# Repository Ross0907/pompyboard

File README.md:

# Wonkle

Wonkle builds gaming hardware such as tablets and keypads for gamers.
Source code, 3D models, schematics, etc. are available under
[OSI-Approved Software and Hardware Licenses](https://opensource.org/licenses). We welcome everyone
to contribute and join us in our quest to make the best hardware for our fellow gamers.

## [Frequently Asked Questions](https://docs.wonkle.io/faq.html)

## Star History

## Contributors

Wonkle is built by people like you.

## License

Different parts of the project are available under different licenses.

All image, audio, and other resources are, unless otherwise specified, available under
[`CC-BY-4.0`](https://spdx.org/licenses/CC-BY-4.0.html).

The hardware designs are, unless otherwise specified, available under
[`CERN-OHL-S-2.0`](https://spdx.org/licenses/CERN-OHL-S-2.0.html).

All other code are, unless otherwise specified, available under
[`MIT`](https://spdx.org/licenses/MIT.html).

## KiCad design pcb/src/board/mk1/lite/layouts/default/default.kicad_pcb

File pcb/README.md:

# PCB

Designed with [KiCad][kicad].

## Designing

- Every PCB is designed with KiCad `v10.0.3`.
- you can learn more about each of the components and read their documentations at
  [`docs/components`](./docs/components/README.md).
  Running `bun run gen-docs` will download PDF documentations.

## Manufacturing

Both prototype and production PCB is manufactured by [JLCPCB][jlcpcb].

### Steps

1. Install [KiCad][kicad].
2. Install the [Fabrication Toolkit][fab-toolkit] plugin.
3. "Generate" production files using the plugin with default settings.
4. Go to [jlcpcb.com][jlcpcb] and click "Add gerber file"
5. Select `pcb/production/wonkle.zip`
6. Configure PCB (you will get 5 pcb of which 2 have components soldered)
   - PCB Specifications
     - PCB Thickness - 1.0mm
     - Surface Finish - LeadFree HASL (health is important boiz)
   - High-spec Options
     - Confirm Production file - Yes
     - Mark on PCB - Order Number(Specify Position)
   - PCB Assembly
     - PCBA Qty - minimum is 2
     - Confirm Parts Placement - Yes
     - Advanced
       - Board Cleaning - Yes
7. Press "NEXT"
8. Inspect PCB and press "NEXT" again
9. Upload and process `pcb/production/bom.csv` and `pcb/production/positions.csv`
10. Review the parts and press "NEXT"
11. Fix component placement
    - only J2 (1x4 pin) needs manual edit
12. Select `Research\Education\DIY\Entertainment > DIY Hobby Circuit Board - HS Code 902300` in Quote & Order section. The total price is 137.13 USD as of writing.
13. Press "SAVE TO CART"
14. Select both PCB and PCBA then click "Secure Checkout"
15. Enter shipping info and follow JLCPCB's instruction (e.g. production file confirmation)
16. Wait for a week and you'll receive your very own board!

[kicad]: https://www.kicad.org/
[jlcpcb]: https://jlcpcb.com/
[fab-toolkit]: https://github.com/bennymeg/Fabrication-Toolkit

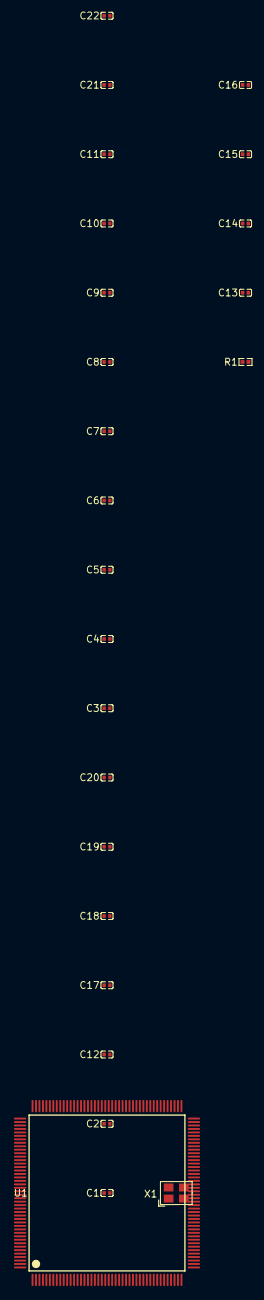
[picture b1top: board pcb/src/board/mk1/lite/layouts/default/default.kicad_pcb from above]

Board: 2 copper layers, 25 parts (0 on the bottom side), 7 nets, no tracks yet.

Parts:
C1: 4.7µF ±20%; C0402
C2, C3, C4, C5, C6, C7, C8, C9, C10, C11, C12, C17, C18, C19, C20: 100nF ±10%; C0402
C13, C14: 20pF ±5%; C0402
C15, C16: 2.2µF ±20%; C0402
C21: 1µF ±10%; C0402
C22: 10nF ±10%; C0402
R1: 1kΩ ±1%; R0402
U1: LQFP-176_L24.0-W24.0-P0.50-LS26.0-BL
X1: CRYSTAL-SMD_4P-L3.2-W2.5-BL-2

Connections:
XIN: C13.1, U1.29, X1.1
XOUT: R1.2, U1.30
hse_load_caps[1]-power-hv: C14.1, R1.1, X1.3
hv: C1.1, C2.1, C3.1, C4.1, C5.1, C6.1, C7.1, C8.1, C9.1, C10.1, C11.1, C12.1, C17.1, C18.1, C19.1, C20.1, C21.1, C22.1, U1.6, U1.15, U1.23, U1.36, U1.38, U1.39, U1.49, U1.62, U1.72, U1.82, U1.91, U1.103, U1.114, U1.127, U1.136, U1.149, U1.159, U1.172
lv: C1.2, C2.2, C3.2, C4.2, C5.2, C6.2, C7.2, C8.2, C9.2, C10.2, C11.2, C12.2, C13.2, C14.2, C15.2, C16.2, C17.2, C18.2, C19.2, C20.2, C21.2, C22.2, U1.14, U1.22, U1.37, U1.61, U1.71, U1.90, U1.102, U1.113, U1.126, U1.135, U1.148, U1.158, X1.2, X1.4
vcap_caps[0]-power-hv: C15.1, U1.81
vcap_caps[1]-power-hv: C16.1, U1.125

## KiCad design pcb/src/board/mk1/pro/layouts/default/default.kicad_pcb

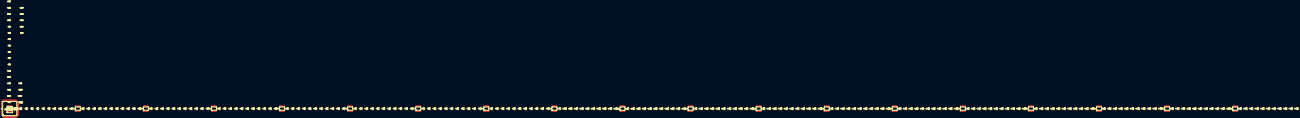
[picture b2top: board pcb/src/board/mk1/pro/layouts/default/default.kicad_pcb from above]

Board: 2 copper layers, 260 parts (0 on the bottom side), 243 nets, no tracks yet.

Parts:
C1: 4.7µF ±20%; C0402
C2, C3, C4, C5, C6, C7, C8, C9, C10, C11, C12, C17, C18, C22, C23: 100nF ±10%; C0402
C13, C14: 20pF ±5%; C0402
C15, C16: 2.2µF ±20%; C0402
C19: 10µF ±20%; C0402
C20: 22µF ±20%; C0402
C21: 3.3nF ±10%; C0402
C24: 1µF ±10%; C0402
C25: 10nF ±10%; C0402
L1: L 2.2µH ±10%; L0805
R1: 1kΩ ±1%; R0402
R2: 100kΩ ±1%; R0603
U1: LQFP-176_L24.0-W24.0-P0.50-LS26.0-BL
U2, U14, U26, U38, U50, U62, U74, U86, U98, U110, U122, U134, U146, U158, U170, U182, U194, U206, U218: SSOP-24_L8.1-W5.3-P0.65-LS7.8-BL
U3, U4, U5, U6, U7, U8, U9, U10, U11, U12, U13, U15, U16, U17, U18, U19, U20, U21, U22, U23, U24, U25, U27, U28, U29, U30, U31, U32, U33, U34, U35, U36, U37, U39, U40, U41, U42, U43, U44, U45, U46, U47, U48, U49, U51, U52, U53, U54, U55, U56, U57, U58, U59, U60, U61, U63, U64, U65, U66, U67, U68, U69, U70, U71, U72, U73, U75, U76, U77, U78, U79, U80, U81, U82, U83, U84, U85, U87, U88, U89, U90, U91, U92, U93, U94, U95, U96, U97, U99, U100, U101, U102, U103, U104, U105, U106, U107, U108, U109, U111, U112, U113, U114, U115, U116, U117, U118, U119, U120, U121, U123, U124, U125, U126, U127, U128, U129, U130, U131, U132, U133, U135, U136, U137, U138, U139, U140, U141, U142, U143, U144, U145, U147, U148, U149, U150, U151, U152, U153, U154, U155, U156, U157, U159, U160, U161, U162, U163, U164, U165, U166, U167, U168, U169, U171, U172, U173, U174, U175, U176, U177, U178, U179, U180, U181, U183, U184, U185, U186, U187, U188, U189, U190, U191, U192, U193, U195, U196, U197, U198, U199, U200, U201, U202, U203, U204, U205, U207, U208, U209, U210, U211, U212, U213, U214, U215, U216, U217, U219, U220, U221, U222, U223, U224, U225, U226, U227, U228, U229: SOT-23-3_L2.9-W1.6-P1.90-LS2.8-BR
U230: TQFN-16_L3.0-W3.0-P0.50-TL-EP1.7
USB1: USC-C-SMD_USB4085-GF-A
X1: CRYSTAL-SMD_4P-L3.2-W2.5-BL-2

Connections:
2: U2.2, U13.2
OUT: U1.41, U134.1
PG: R2.2, U230.4
S0: U1.5, U2.10, U14.10, U26.10, U38.10, U50.10, U62.10, U74.10, U86.10, U98.10, U110.10, U122.10, U134.10, U146.10, U158.10, U170.10, U182.10, U194.10, U206.10, U218.10
S1: U1.4, U2.11, U14.11, U26.11, U38.11, U50.11, U62.11, U74.11, U86.11, U98.11, U110.11, U122.11, U134.11, U146.11, U158.11, U170.11, U182.11, U194.11, U206.11, U218.11
S2: U1.3, U2.14, U14.14, U26.14, U38.14, U50.14, U62.14, U74.14, U86.14, U98.14, U110.14, U122.14, U134.14, U146.14, U158.14, U170.14, U182.14, U194.14, U206.14, U218.14
S3: U1.2, U2.13, U14.13, U26.13, U38.13, U50.13, U62.13, U74.13, U86.13, U98.13, U110.13, U122.13, U134.13, U146.13, U158.13, U170.13, U182.13, U194.13, U206.13, U218.13
SW: L1.1, U230.1, U230.2, U230.3
XIN: C13.1, U1.29, X1.1
XOUT: R1.2, U1.30
gpio_a[2]-OUT: U1.42, U146.1
gpio_a[3]-OUT: U1.47, U158.1
gpio_a[4]-OUT: U1.50, U170.1
gpio_a[6]-OUT: U1.52, U182.1
gpio_a[7]-OUT: U1.53, U194.1
gpio_c[2]-OUT: U1.34, U110.1
gpio_c[3]-OUT: U1.35, U122.1
gpio_c[4]-OUT: U1.54, U206.1
gpio_c[5]-OUT: U1.55, U218.1
gpio_f[3]-OUT: U1.19, U2.1
gpio_f[4]-OUT: U1.20, U14.1
gpio_f[5]-OUT: U1.21, U26.1
gpio_f[6]-OUT: U1.24, U38.1
gpio_f[7]-OUT: U1.25, U50.1
gpio_f[8]-OUT: U1.26, U62.1
gpio_f[9]-OUT: U1.27, U74.1
gpio_f[10]-OUT: U1.28, U86.1
hse_load_caps[1]-power-hv: C14.1, R1.1, X1.3
hv: C19.1, U230.10, U230.11, U230.12, U230.13, USB1.A4, USB1.A9, USB1.B4, USB1.B9
i2c[1]-SDA: U1.33, U98.1
lv: C1.2, C2.2, C3.2, C4.2, C5.2, C6.2, C7.2, C8.2, C9.2, C10.2, C11.2, C12.2, C13.2, C14.2, C15.2, C16.2, C17.2, C18.2, C19.2, C20.2, C21.2, C22.2, C23.2, C24.2, C25.2, U1.14, U1.22, U1.37, U1.61, U1.71, U1.90, U1.102, U1.113, U1.126, U1.135, U1.148, U1.158, U2.12, U2.15, U2.16, U2.17, U2.18, U2.19, U2.20, U3.3, U4.3, U5.3, U6.3, U7.3, U8.3, U9.3, U10.3, U11.3, U12.3, U13.3, U14.12, U14.15, U14.16, U14.17, U14.18, U14.19, U14.20, U15.3, U16.3, U17.3, U18.3, U19.3, U20.3, U21.3, U22.3, U23.3, U24.3, U25.3, U26.12, U26.15, U26.16, U26.17, U26.18, U26.19, U26.20, U27.3, U28.3, U29.3, U30.3, U31.3, U32.3, U33.3, U34.3, U35.3, U36.3, U37.3, U38.12, U38.15, U38.16, U38.17, U38.18, U38.19, U38.20, U39.3, U40.3, U41.3, U42.3, U43.3, U44.3, U45.3, U46.3, U47.3, U48.3, U49.3, U50.12, U50.15, U50.16, U50.17, U50.18, U50.19, U50.20, U51.3, U52.3, U53.3, U54.3, U55.3, U56.3, U57.3, U58.3, U59.3, U60.3, U61.3, U62.12, U62.15, U62.16, U62.17, U62.18, U62.19, U62.20, U63.3, U64.3, U65.3, U66.3, U67.3, U68.3, U69.3, U70.3, U71.3, U72.3, U73.3, U74.12, U74.15, U74.16, U74.17, U74.18, U74.19, U74.20, U75.3, U76.3, U77.3, U78.3, U79.3, U80.3, U81.3, U82.3, U83.3, U84.3, U85.3, U86.12, U86.15, U86.16, U86.17, U86.18, U86.19, U86.20, U87.3, U88.3, U89.3, U90.3, U91.3, U92.3, U93.3, U94.3, U95.3, U96.3, U97.3, U98.12, U98.15, U98.16, U98.17, U98.18, U98.19, U98.20, U99.3, U100.3, U101.3, U102.3, U103.3, U104.3, U105.3, U106.3, U107.3, U108.3, U109.3, U110.12, U110.15, U110.16, U110.17, U110.18, U110.19, U110.20, U111.3, U112.3, U113.3, U114.3, U115.3, U116.3, U117.3, U118.3, U119.3, U120.3, U121.3, U122.12, U122.15, U122.16, U122.17, U122.18, U122.19, U122.20, U123.3, U124.3, U125.3, U126.3, U127.3, U128.3, U129.3, U130.3, U131.3, U132.3, U133.3, U134.12, U134.15, U134.16, U134.17, U134.18, U134.19, U134.20, U135.3, U136.3, U137.3, U138.3, U139.3, U140.3, U141.3, U142.3, U143.3, U144.3, U145.3, U146.12, U146.15, U146.16, U146.17, U146.18, U146.19, U146.20, U147.3, U148.3, U149.3, U150.3, U151.3, U152.3, U153.3, U154.3, U155.3, U156.3, U157.3, U158.12, U158.15, U158.16, U158.17, U158.18, U158.19, U158.20, U159.3, U160.3, U161.3, U162.3, U163.3, U164.3, U165.3, U166.3, U167.3, U168.3, U169.3, U170.12, U170.15, U170.16, U170.17, U170.18, U170.19, U170.20, U171.3, U172.3, U173.3, U174.3, U175.3, U176.3, U177.3, U178.3, U179.3, U180.3, U181.3, U182.12, U182.15, U182.16, U182.17, U182.18, U182.19, U182.20, U183.3, U184.3, U185.3, U186.3, U187.3, U188.3, U189.3, U190.3, U191.3, U192.3, U193.3, U194.12, U194.15, U194.16, U194.17, U194.18, U194.19, U194.20, U195.3, U196.3, U197.3, U198.3, U199.3, U200.3, U201.3, U202.3, U203.3, U204.3, U205.3, U206.12, U206.15, U206.16, U206.17, U206.18, U206.19, U206.20, U207.3, U208.3, U209.3, U210.3, U211.3, U212.3, U213.3, U214.3, U215.3, U216.3, U217.3, U218.12, U218.15, U218.16, U218.17, U218.18, U218.19, U218.20, U219.3, U220.3, U221.3, U222.3, U223.3, U224.3, U225.3, U226.3, U227.3, U228.3, U229.3, U230.5, U230.6, U230.7, U230.8, U230.15, U230.16, USB1.A1, USB1.A12, USB1.B1, USB1.B12, X1.2, X1.4
mux-OUT: U2.21, U3.2
mux-OUT-1: U2.22, U4.2
mux-OUT-2: U2.23, U5.2
mux-OUT-3: U2.3, U12.2
mux-OUT-4: U2.4, U11.2
mux-OUT-5: U2.5, U10.2
mux-OUT-6: U2.6, U9.2
mux-OUT-7: U2.7, U8.2
mux-OUT-8: U2.8, U7.2
mux-OUT-9: U2.9, U6.2
mux-OUT-10: U122.21, U123.2
mux-OUT-11: U122.22, U124.2
mux-OUT-12: U122.23, U125.2
mux-OUT-13: U122.3, U132.2
mux-OUT-14: U122.4, U131.2
mux-OUT-15: U122.5, U130.2
mux-OUT-16: U122.6, U129.2
mux-OUT-17: U122.7, U128.2
mux-OUT-18: U122.8, U127.2
mux-OUT-19: U122.9, U126.2
mux-OUT-20: U134.21, U135.2
mux-OUT-21: U134.22, U136.2
mux-OUT-22: U134.23, U137.2
mux-OUT-23: U134.3, U144.2
mux-OUT-24: U134.4, U143.2
mux-OUT-25: U134.5, U142.2
mux-OUT-26: U134.6, U141.2
mux-OUT-27: U134.7, U140.2
mux-OUT-28: U134.8, U139.2
mux-OUT-29: U134.9, U138.2
mux-OUT-30: U146.21, U147.2
mux-OUT-31: U146.22, U148.2
mux-OUT-32: U146.23, U149.2
mux-OUT-33: U146.3, U156.2
mux-OUT-34: U146.4, U155.2
mux-OUT-35: U146.5, U154.2
mux-OUT-36: U146.6, U153.2
mux-OUT-37: U146.7, U152.2
mux-OUT-38: U146.8, U151.2
mux-OUT-39: U146.9, U150.2
mux-OUT-40: U158.21, U159.2
mux-OUT-41: U158.22, U160.2
mux-OUT-42: U158.23, U161.2
mux-OUT-43: U158.3, U168.2
mux-OUT-44: U158.4, U167.2
mux-OUT-45: U158.5, U166.2
mux-OUT-46: U158.6, U165.2
mux-OUT-47: U158.7, U164.2
mux-OUT-48: U158.8, U163.2
mux-OUT-49: U158.9, U162.2
mux-OUT-50: U170.21, U171.2
mux-OUT-51: U170.22, U172.2
mux-OUT-52: U170.23, U173.2
mux-OUT-53: U170.3, U180.2
mux-OUT-54: U170.4, U179.2
mux-OUT-55: U170.5, U178.2
mux-OUT-56: U170.6, U177.2
mux-OUT-57: U170.7, U176.2
mux-OUT-58: U170.8, U175.2
mux-OUT-59: U170.9, U174.2
mux-OUT-60: U182.21, U183.2
mux-OUT-61: U182.22, U184.2
mux-OUT-62: U182.23, U185.2
mux-OUT-63: U182.3, U192.2
mux-OUT-64: U182.4, U191.2
mux-OUT-65: U182.5, U190.2
mux-OUT-66: U182.6, U189.2
mux-OUT-67: U182.7, U188.2
mux-OUT-68: U182.8, U187.2
mux-OUT-69: U182.9, U186.2
mux-OUT-70: U194.21, U195.2
mux-OUT-71: U194.22, U196.2
mux-OUT-72: U194.23, U197.2
mux-OUT-73: U194.3, U204.2
mux-OUT-74: U194.4, U203.2
mux-OUT-75: U194.5, U202.2
mux-OUT-76: U194.6, U201.2
mux-OUT-77: U194.7, U200.2
mux-OUT-78: U194.8, U199.2
mux-OUT-79: U194.9, U198.2
mux-OUT-80: U206.21, U207.2
mux-OUT-81: U206.22, U208.2
mux-OUT-82: U206.23, U209.2
mux-OUT-83: U206.3, U216.2
mux-OUT-84: U206.4, U215.2
mux-OUT-85: U206.5, U214.2
mux-OUT-86: U206.6, U213.2
mux-OUT-87: U206.7, U212.2
mux-OUT-88: U206.8, U211.2
mux-OUT-89: U206.9, U210.2
mux-OUT-90: U218.21, U219.2
mux-OUT-91: U218.22, U220.2
mux-OUT-92: U218.23, U221.2
mux-OUT-93: U218.3, U228.2
mux-OUT-94: U218.4, U227.2
mux-OUT-95: U218.5, U226.2
mux-OUT-96: U218.6, U225.2
mux-OUT-97: U218.7, U224.2
mux-OUT-98: U218.8, U223.2
mux-OUT-99: U218.9, U222.2
mux-OUT-100: U14.21, U15.2
mux-OUT-101: U14.22, U16.2
mux-OUT-102: U14.23, U17.2
mux-OUT-103: U14.3, U24.2
mux-OUT-104: U14.4, U23.2
mux-OUT-105: U14.5, U22.2
mux-OUT-106: U14.6, U21.2
mux-OUT-107: U14.7, U20.2
mux-OUT-108: U14.8, U19.2
mux-OUT-109: U14.9, U18.2
mux-OUT-110: U26.21, U27.2
mux-OUT-111: U26.22, U28.2
mux-OUT-112: U26.23, U29.2
mux-OUT-113: U26.3, U36.2
mux-OUT-114: U26.4, U35.2
mux-OUT-115: U26.5, U34.2
mux-OUT-116: U26.6, U33.2
mux-OUT-117: U26.7, U32.2
mux-OUT-118: U26.8, U31.2
mux-OUT-119: U26.9, U30.2
mux-OUT-120: U38.21, U39.2
mux-OUT-121: U38.22, U40.2
mux-OUT-122: U38.23, U41.2
mux-OUT-123: U38.3, U48.2
mux-OUT-124: U38.4, U47.2
mux-OUT-125: U38.5, U46.2
mux-OUT-126: U38.6, U45.2
mux-OUT-127: U38.7, U44.2
mux-OUT-128: U38.8, U43.2
mux-OUT-129: U38.9, U42.2
mux-OUT-130: U50.21, U51.2
mux-OUT-131: U50.22, U52.2
mux-OUT-132: U50.23, U53.2
mux-OUT-133: U50.3, U60.2
mux-OUT-134: U50.4, U59.2
mux-OUT-135: U50.5, U58.2
mux-OUT-136: U50.6, U57.2
mux-OUT-137: U50.7, U56.2
mux-OUT-138: U50.8, U55.2
mux-OUT-139: U50.9, U54.2
mux-OUT-140: U62.21, U63.2
mux-OUT-141: U62.22, U64.2
mux-OUT-142: U62.23, U65.2
mux-OUT-143: U62.3, U72.2
mux-OUT-144: U62.4, U71.2
mux-OUT-145: U62.5, U70.2
mux-OUT-146: U62.6, U69.2
mux-OUT-147: U62.7, U68.2
mux-OUT-148: U62.8, U67.2
mux-OUT-149: U62.9, U66.2
mux-OUT-150: U74.21, U75.2
mux-OUT-151: U74.22, U76.2
mux-OUT-152: U74.23, U77.2
mux-OUT-153: U74.3, U84.2
mux-OUT-154: U74.4, U83.2
mux-OUT-155: U74.5, U82.2
mux-OUT-156: U74.6, U81.2
mux-OUT-157: U74.7, U80.2
mux-OUT-158: U74.8, U79.2
mux-OUT-159: U74.9, U78.2
mux-OUT-160: U86.21, U87.2
mux-OUT-161: U86.22, U88.2
mux-OUT-162: U86.23, U89.2
mux-OUT-163: U86.3, U96.2
mux-OUT-164: U86.4, U95.2
mux-OUT-165: U86.5, U94.2
mux-OUT-166: U86.6, U93.2
mux-OUT-167: U86.7, U92.2
mux-OUT-168: U86.8, U91.2
mux-OUT-169: U86.9, U90.2
mux-OUT-170: U98.21, U99.2
mux-OUT-171: U98.22, U100.2
mux-OUT-172: U98.23, U101.2
mux-OUT-173: U98.3, U108.2
mux-OUT-174: U98.4, U107.2
mux-OUT-175: U98.5, U106.2
mux-OUT-176: U98.6, U105.2
mux-OUT-177: U98.7, U104.2
mux-OUT-178: U98.8, U103.2
mux-OUT-179: U98.9, U102.2
mux-OUT-180: U110.21, U111.2
mux-OUT-181: U110.22, U112.2
mux-OUT-182: U110.23, U113.2
mux-OUT-183: U110.3, U120.2
mux-OUT-184: U110.4, U119.2
mux-OUT-185: U110.5, U118.2
mux-OUT-186: U110.6, U117.2
mux-OUT-187: U110.7, U116.2
mux-OUT-188: U110.8, U115.2
mux-OUT-189: U110.9, U114.2
mux_columns[1]-2: U14.2, U25.2
mux_columns[2]-2: U26.2, U37.2
mux_columns[3]-2: U38.2, U49.2
mux_columns[4]-2: U50.2, U61.2
mux_columns[5]-2: U62.2, U73.2
mux_columns[6]-2: U74.2, U85.2
mux_columns[7]-2: U86.2, U97.2
mux_columns[8]-2: U98.2, U109.2
mux_columns[9]-2: U110.2, U121.2
mux_columns[10]-2: U122.2, U133.2
mux_columns[11]-2: U134.2, U145.2
mux_columns[12]-2: U146.2, U157.2
mux_columns[13]-2: U158.2, U169.2
mux_columns[14]-2: U170.2, U181.2
mux_columns[15]-2: U182.2, U193.2
mux_columns[16]-2: U194.2, U205.2
mux_columns[17]-2: U206.2, U217.2
mux_columns[18]-2: U218.2, U229.2
out_cap-power-hv: C1.1, C2.1, C3.1, C4.1, C5.1, C6.1, C7.1, C8.1, C9.1, C10.1, C11.1, C12.1, C17.1, C18.1, C20.1, C22.1, C23.1, C24.1, C25.1, L1.2, R2.1, U1.6, U1.15, U1.23, U1.36, U1.38, U1.39, U1.49, U1.62, U1.72, U1.82, U1.91, U1.103, U1.114, U1.127, U1.136, U1.149, U1.159, U1.172, U2.24, U3.1, U4.1, U5.1, U6.1, U7.1, U8.1, U9.1, U10.1, U11.1, U12.1, U13.1, U14.24, U15.1, U16.1, U17.1, U18.1, U19.1, U20.1, U21.1, U22.1, U23.1, U24.1, U25.1, U26.24, U27.1, U28.1, U29.1, U30.1, U31.1, U32.1, U33.1, U34.1, U35.1, U36.1, U37.1, U38.24, U39.1, U40.1, U41.1, U42.1, U43.1, U44.1, U45.1, U46.1, U47.1, U48.1, U49.1, U50.24, U51.1, U52.1, U53.1, U54.1, U55.1, U56.1, U57.1, U58.1, U59.1, U60.1, U61.1, U62.24, U63.1, U64.1, U65.1, U66.1, U67.1, U68.1, U69.1, U70.1, U71.1, U72.1, U73.1, U74.24, U75.1, U76.1, U77.1, U78.1, U79.1, U80.1, U81.1, U82.1, U83.1, U84.1, U85.1, U86.24, U87.1, U88.1, U89.1, U90.1, U91.1, U92.1, U93.1, U94.1, U95.1, U96.1, U97.1, U98.24, U99.1, U100.1, U101.1, U102.1, U103.1, U104.1, U105.1, U106.1, U107.1, U108.1, U109.1, U110.24, U111.1, U112.1, U113.1, U114.1, U115.1, U116.1, U117.1, U118.1, U119.1, U120.1, U121.1, U122.24, U123.1, U124.1, U125.1, U126.1, U127.1, U128.1, U129.1, U130.1, U131.1, U132.1, U133.1, U134.24, U135.1, U136.1, U137.1, U138.1, U139.1, U140.1, U141.1, U142.1, U143.1, U144.1, U145.1, U146.24, U147.1, U148.1, U149.1, U150.1, U151.1, U152.1, U153.1, U154.1, U155.1, U156.1, U157.1, U158.24, U159.1, U160.1, U161.1, U162.1, U163.1, U164.1, U165.1, U166.1, U167.1, U168.1, U169.1, U170.24, U171.1, U172.1, U173.1, U174.1, U175.1, U176.1, U177.1, U178.1, U179.1, U180.1, U181.1, U182.24, U183.1, U184.1, U185.1, U186.1, U187.1, U188.1, U189.1, U190.1, U191.1, U192.1, U193.1, U194.24, U195.1, U196.1, U197.1, U198.1, U199.1, U200.1, U201.1, U202.1, U203.1, U204.1, U205.1, U206.24, U207.1, U208.1, U209.1, U210.1, U211.1, U212.1, U213.1, U214.1, U215.1, U216.1, U217.1, U218.24, U219.1, U220.1, U221.1, U222.1, U223.1, U224.1, U225.1, U226.1, U227.1, U228.1, U229.1, U230.14
ss_tr_cap-power-hv: C21.1, U230.9
vcap_caps[0]-power-hv: C15.1, U1.81
vcap_caps[1]-power-hv: C16.1, U1.125

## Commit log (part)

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2026-05-06 web: update react (security patch)
2026-05-06 update mise lockfile
2026-05-29 Update PCB with HSE oscillator, Footprint Mismatch fix and Rename project files to Wonkle (#36)
2026-05-29 update license
2026-05-29 put mk1 hardware design under its own subdirectory
2026-05-29 init wonkleboard mk.1 lite as empty atopile project
2026-05-29 automate spelling checks
2026-06-01 pcb: add basic STM32F429 MCU module
2026-06-01 ignore spelling of non-handwritten files
2026-06-02 define and apply github labels
2026-06-02 make github action happy
2026-06-02 rename `type:suggestion` label to `type:proposition`
2026-06-02 rename workflow job to be more appropriate
2026-06-02 order labels alphabetically
2026-06-02 docs: improve clarity in language
2026-06-02 simplify vscode config
2026-06-02 remove unnecessary words from cspell.yaml
2026-06-04 create space to redesign wonkleboard mk.1 pro with atopile
2026-06-04 pcb: initialize Wonkleboard mk.1 Pro atopile project
2026-06-04 pcb: make atopile source code consistent
2026-06-04 pcb: make CI build more robust
2026-06-05 pcb: remove unnecessary pragma directives
2026-06-05 pcb: add MCU to Wonkleboard mk.1 Pro
2026-06-09 make ./scripts intellisense work in vscode
2026-06-09 spell check dot directories
2026-06-13 firmware: run cargo audit in CI
2026-06-13 firmware: disable cargo audit for now
2026-06-16 make firmware work somewhat
2026-06-16 remove unnecessary svd file
2026-06-16 firmware: update stm32f4xx-hal
2026-06-22 pcb: add MUX and sensors to Wonkleboard mk.1 Pro
2026-06-22 pcb: oops forgot to commit this
2026-06-23 pcb: add buck converter
2026-06-23 pcb: add STM32 ADC application note
2026-06-24 pcb: document ADC-capable pins
2026-06-24 pcb: add more bookmarks for STM32F429 datasheet and reference manual
2026-06-24 firmware: add link to HAL source code
2026-06-24 firmware: mention microprocessor docs in README
2026-06-25 pcb: add more references to documentation
2026-06-25 pcb: add decoupling capacitors to STM32F429
2026-06-25 add AGENTS.md
2026-06-27 firmware: v0.1 baseline (#61)
2026-06-27 fix cspell prune script
2026-06-27 pcb: migrate from atopile to tscircuit (tsci init)
2026-06-27 pcb: add PDF files to gitignore
2026-06-27 pcb: add STM32F429IGT6
2026-06-27 pcb: add KiCad files to gitignore
2026-06-27 pcb: add AH49HSC
2026-06-27 pcb: sort imports
2026-06-27 pcb: check formatting in CI
2026-06-27 pcb: add JLCPCB link to imports
2026-06-27 pcb: improve STM32F429IGT6 pin labeling
2026-06-27 pcb: add sensor array
2026-06-27 pcb: add CD74HC4067SM96
2026-06-27 pcb: add TPS62152RGTR
2026-06-27 pcb: abstract out processor module
2026-06-27 pcb: add pinAttributes
2026-06-27 pcb: fix erroneous clearance error (remove when https://github.com/tscircuit/circuit-json-util/pull/101 gets released)
2026-06-27 ci: update PCB build command
2026-06-28 pcb: improve schematic design
2026-06-28 pcb: add USB port
2026-06-28 firmware: make space for firmware for other devices
